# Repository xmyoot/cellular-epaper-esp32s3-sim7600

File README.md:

# Cellular ePaper — ESP32-S3 + SIM7600G-H

Revision B is an **engineering prototype under validation**. It is not released for fabrication or presented as a working, tested device. The portfolio case study remains unpublished pending validation.

This battery-powered design combines an ESP32-S3-WROOM-1-N8, SIM7600G-H LTE modem, GDEY029T94 2.9-inch monochrome ePaper panel interface, and SHT40 temperature/humidity sensor. It uses a protected 1S LiPo, switched modem/display supplies, native USB programming, and 1.8 V UART translation.

## Revision B changes

The initial review found an incorrect modem pinout and footprint, disconnected schematic pins, schematic/PCB disagreement, a SIM protection short, reversed LEDs, unsafe translator enable voltage, and an incompatible display power circuit. Revision B rebuilds the functional schematics and PCB from an explicit pin/net map. See [design report](DESIGN_REPORT.md) and [review results](review/README.md).

To simplify the power architecture, **the battery is charged externally**. USB-C is data/programming only; it does not power or charge the board. The original MCP73831 charger and its unresolved operation under system load have been removed. Use only a protected 1S pack capable of at least 3 A, verify connector polarity, and disconnect the pack for charging.

## Open in KiCad

Use KiCad 10 with the standard libraries installed. Open `Low-Power_Cellular_ePaper_Device_ESP32-S3_SIM7600.kicad_pro`. The project includes its custom 135-pad modem symbol/footprint and six functional schematic sheets. The board is 100 × 80 mm with four copper layers.

- [Component pin/net map](design/rev-b-netmap.json)
- [BOM](BOM.csv): engineering selections; procurement and assembly qualification remain open
- [Bring-up and validation procedure](design/VALIDATION.md)
- [Release status](review/release-status.json)

## CAD review artifacts

[Revision B schematic PDF](review/rev-b/schematic.pdf) · [PCB top CAD view](review/rev-b/pcb-top.png). Native checks report 0 ERC errors (1 retained library warning), 0 PCB DRC violations, 0 open connections and 0 schematic/PCB parity issues. Fabrication requires the [recorded via-in-pad process and stackup qualification](design/FABRICATION_CONSTRAINTS.md).

## Checks and release status

Run `python3 scripts/check_sources.py` for source consistency and `python3 scripts/check_hardware.py` for the audited critical connections. Regenerate native ERC/DRC reports using the commands in [review/README.md](review/README.md).

`python3 scripts/check_release.py` deliberately fails until all manufacturing and physical-validation gates are closed. A clean ERC/DRC result alone does not establish RF performance, battery life, display compatibility, or successful hardware operation.

Original manufacturing files, reports, and renders are retained only as explicitly marked historical material. Do not fabricate from those exports.

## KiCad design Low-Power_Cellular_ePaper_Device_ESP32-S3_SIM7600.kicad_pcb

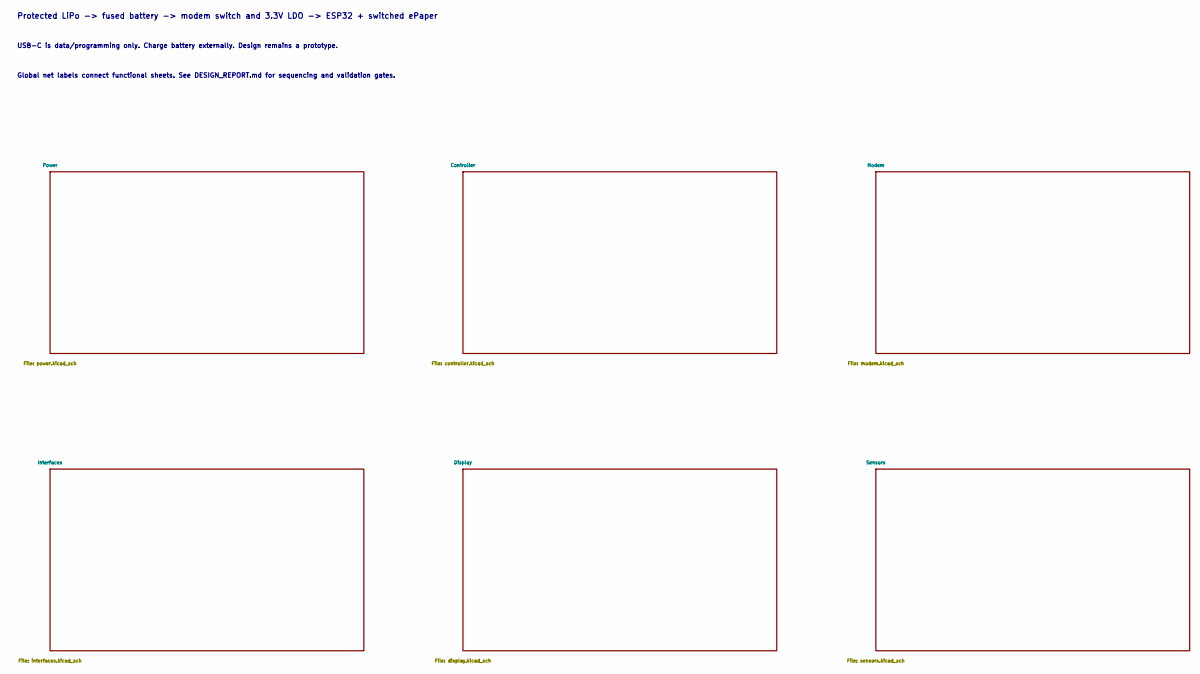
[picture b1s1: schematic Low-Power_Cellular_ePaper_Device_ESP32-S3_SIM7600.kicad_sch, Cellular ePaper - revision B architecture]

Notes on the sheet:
USB-C is data/programming only. Charge battery externally. Design remains a prototype.
Protected LiPo -> fused battery -> modem switch and 3.3V LDO -> ESP32 + switched ePaper
Global net labels connect functional sheets. See DESIGN_REPORT.md for sequencing and validation gates.

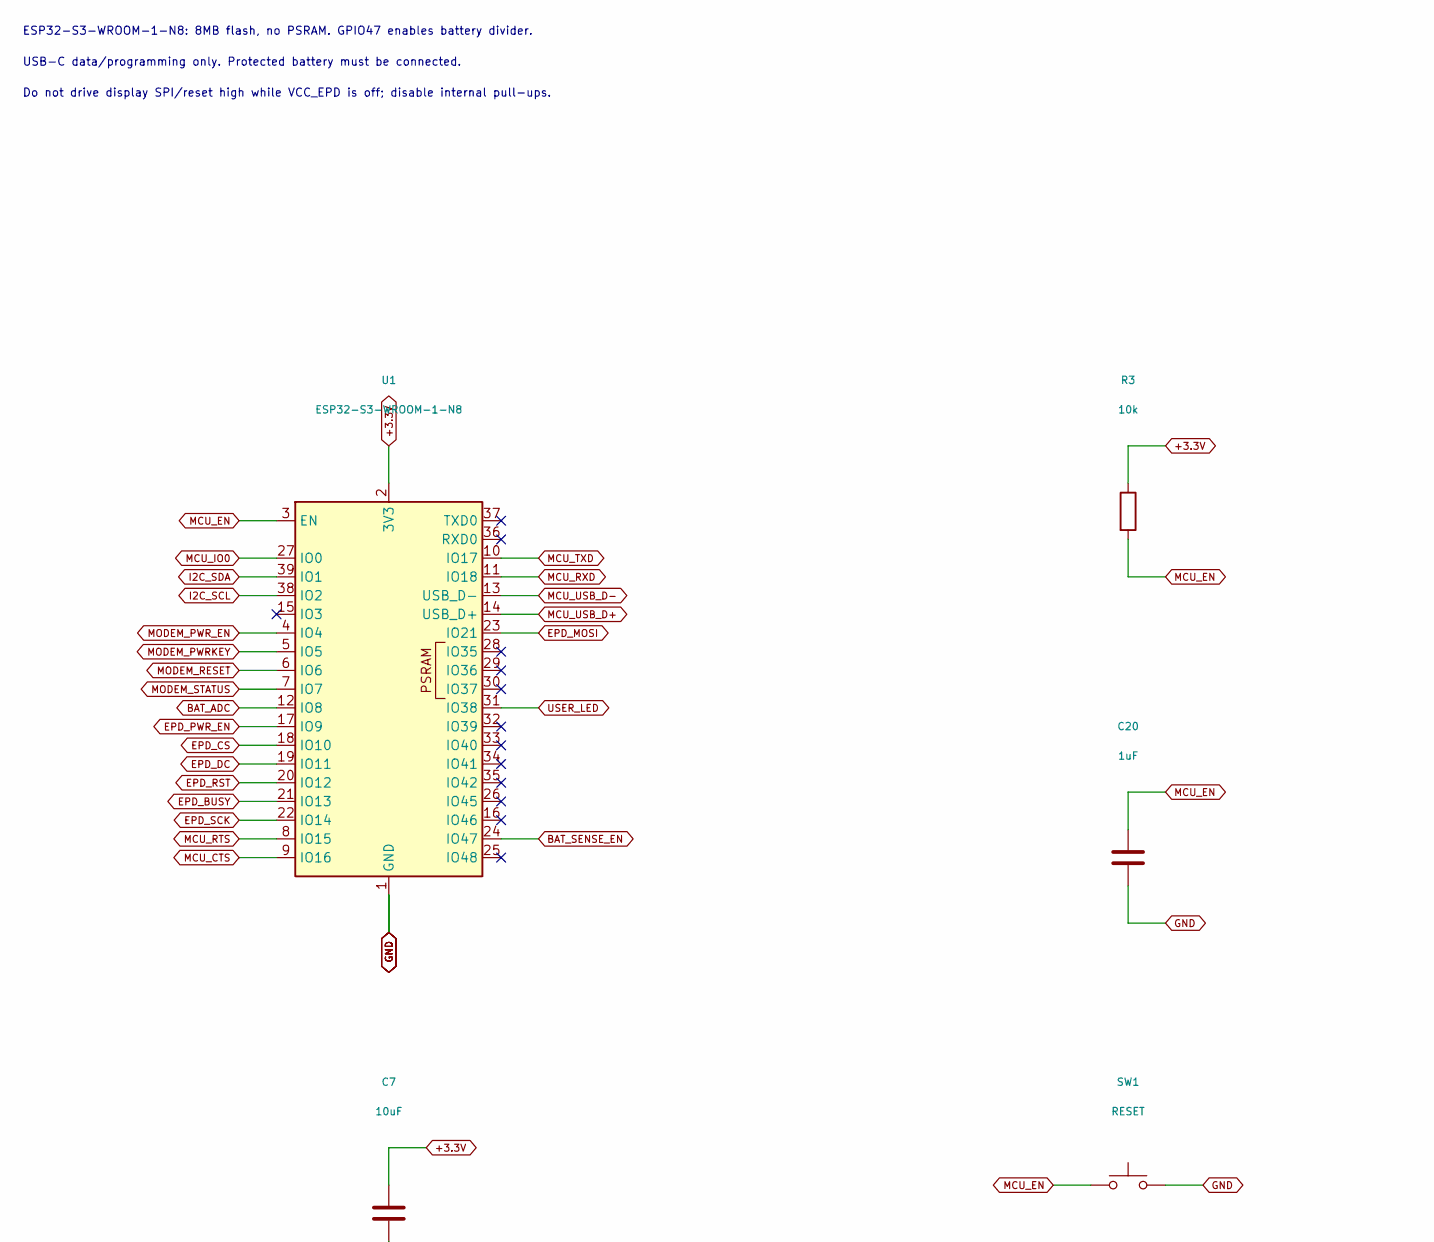
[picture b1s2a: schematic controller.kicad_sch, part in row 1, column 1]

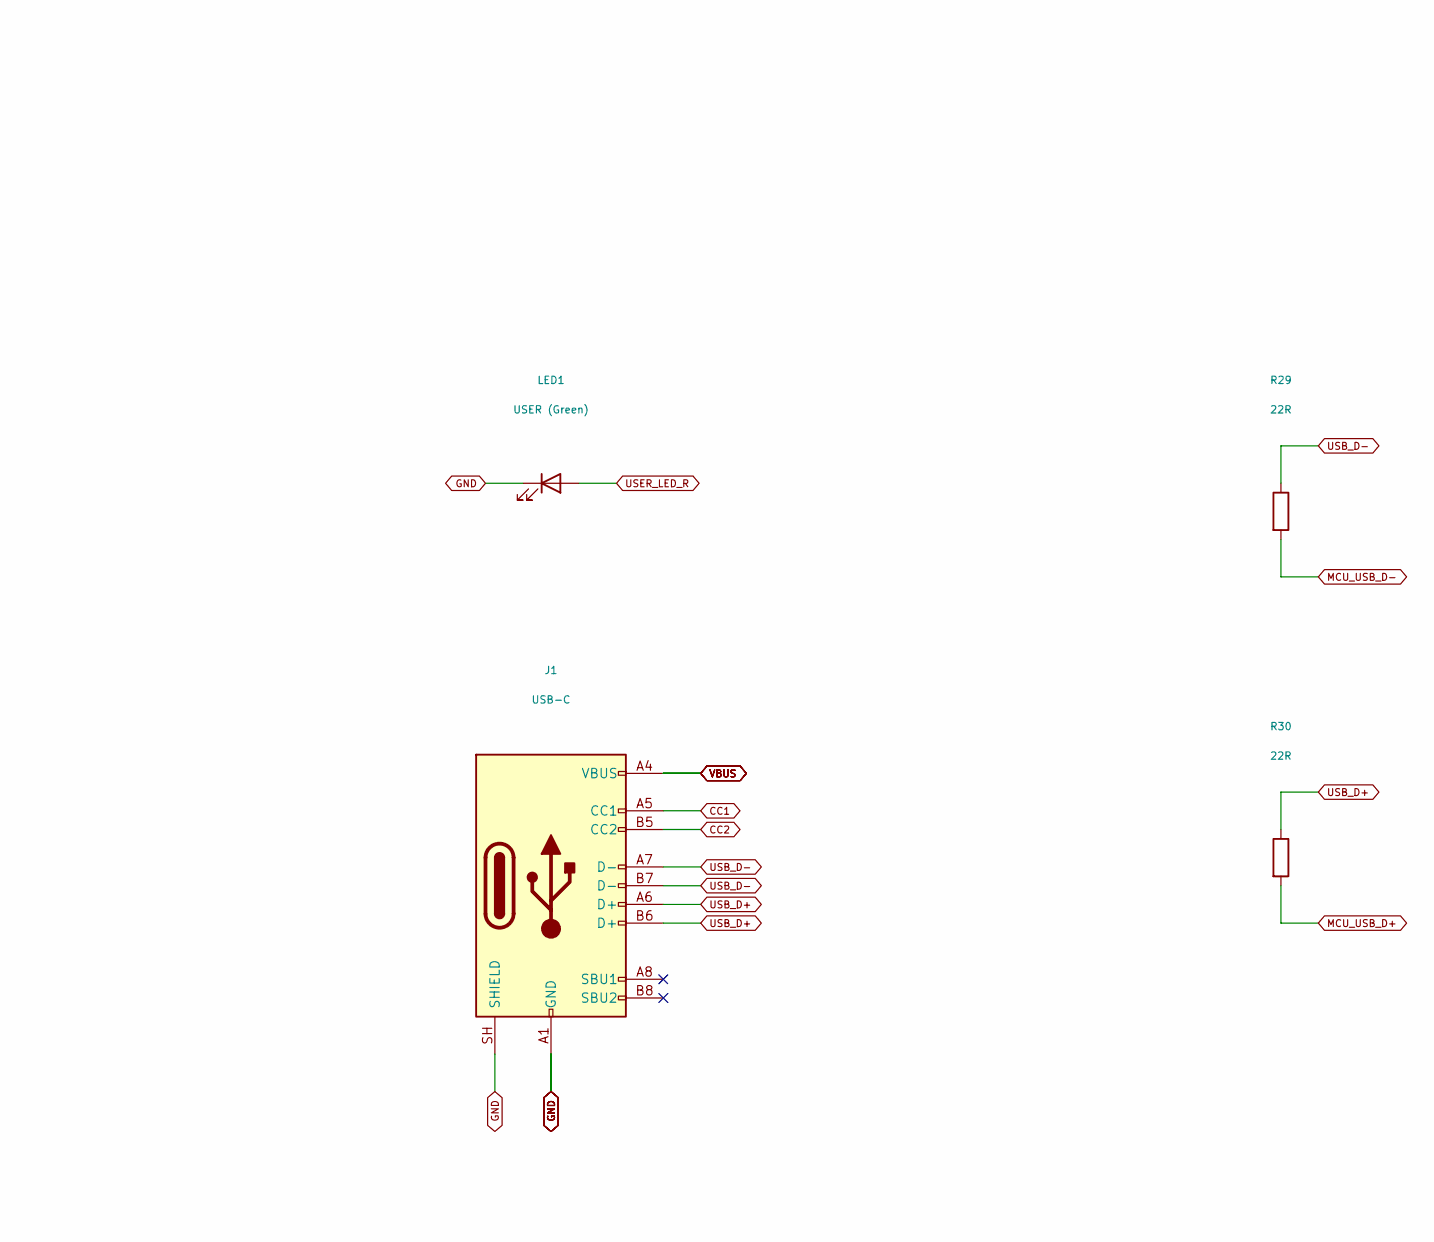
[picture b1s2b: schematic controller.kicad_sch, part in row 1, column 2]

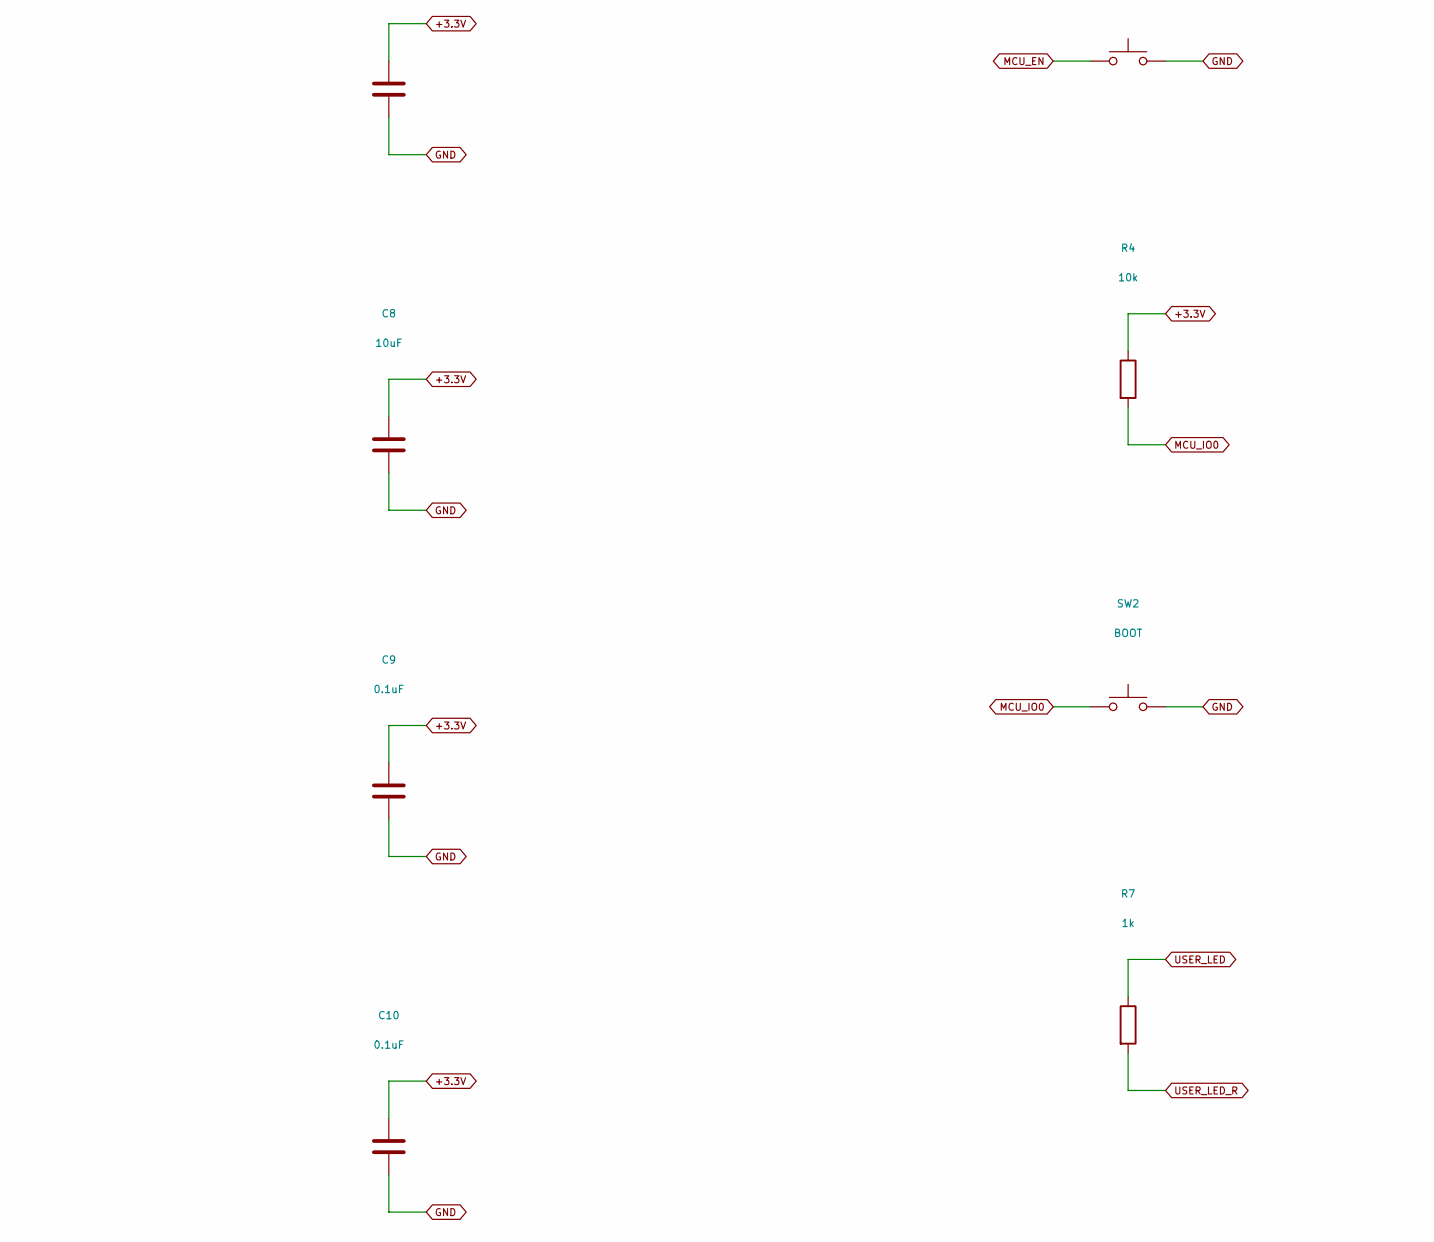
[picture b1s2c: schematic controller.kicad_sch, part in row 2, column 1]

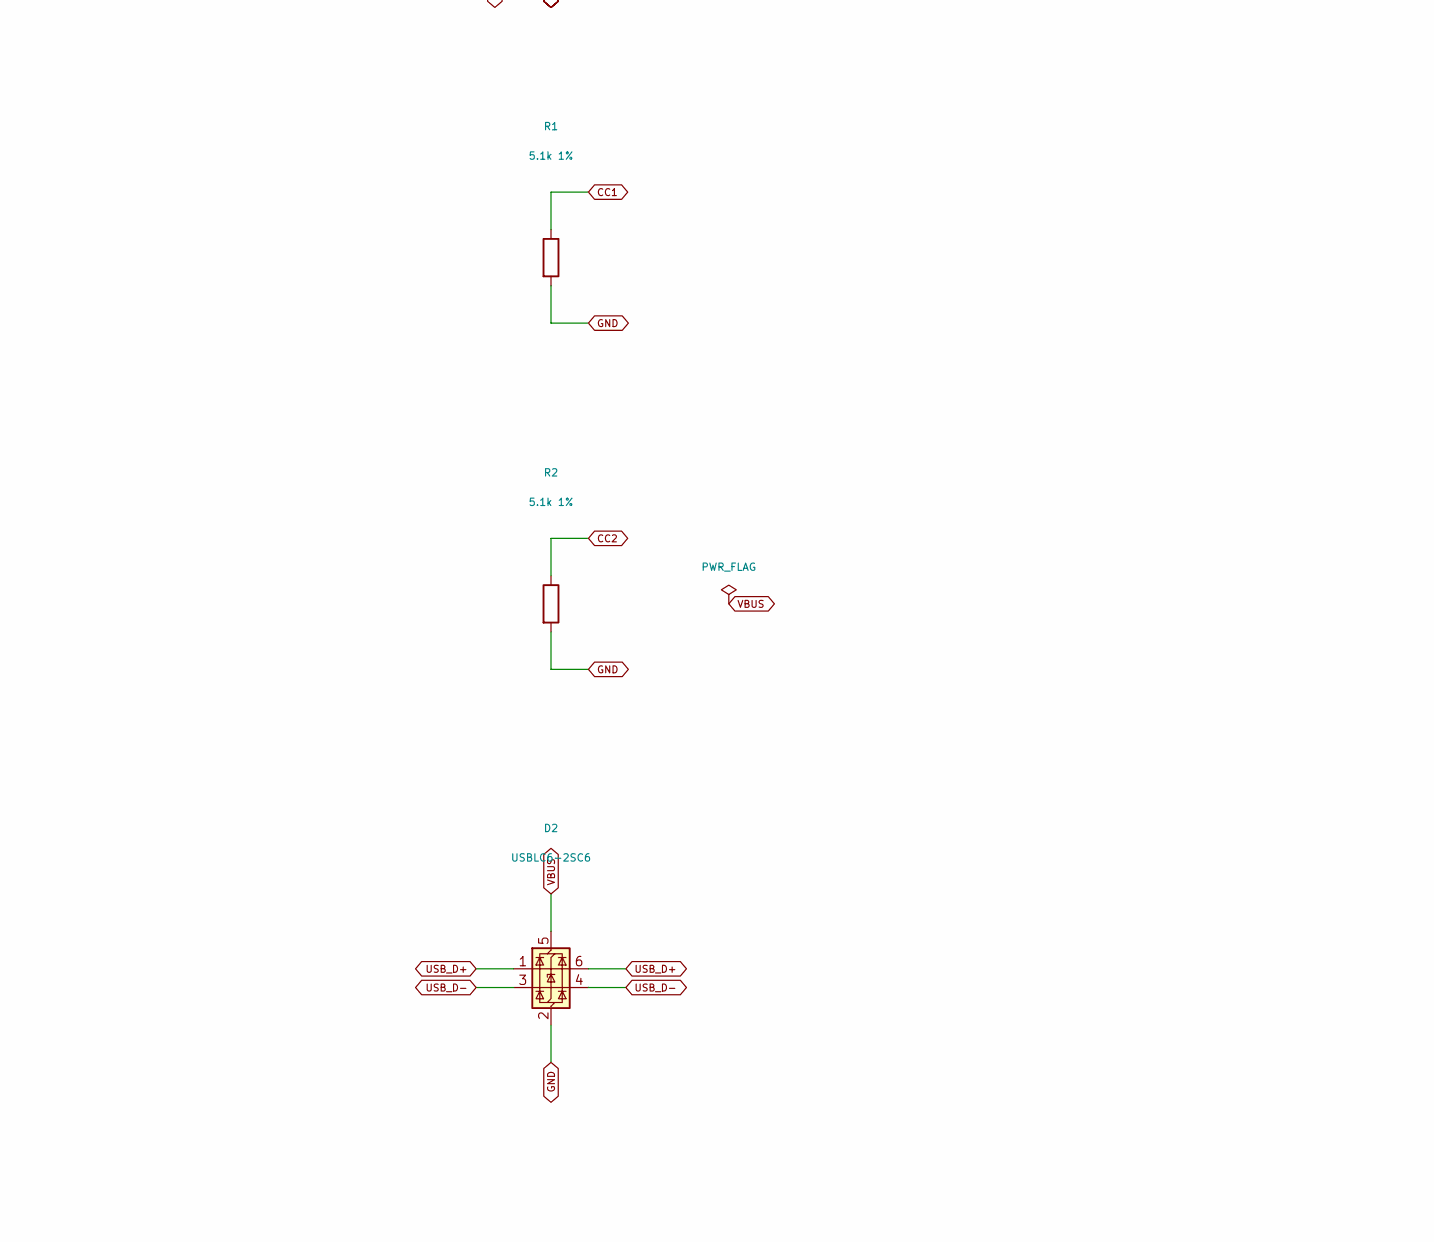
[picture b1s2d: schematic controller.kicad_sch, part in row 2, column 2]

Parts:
C7, C8: 10uF; C_0805_2012Metric
C9, C10: 0.1uF; C_0402_1005Metric
C20: 1uF; C_0603_1608Metric
D2: USBLC6-2SC6; SOT-23-6
J1: USB-C; USB4085_Edge
LED1: USER (Green); LED_0603_1608Metric
R1, R2: 5.1k 1%; R_0603_1608Metric
R3, R4: 10k; R_0603_1608Metric
R7: 1k; R_0603_1608Metric
R29, R30: 22R; R_0603_1608Metric
SW1: RESET; SW_Push_SPST_NO_Alps_SKRK
SW2: BOOT; SW_Push_SPST_NO_Alps_SKRK
U1: ESP32-S3-WROOM-1-N8; ESP32-S3-WROOM-1_Edge

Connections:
+3.3V: C7.1, C8.1, C9.1, C10.1, R3.1, R4.1, U1.2 (3V3); also elsewhere on the board
BAT_ADC: U1.12 (IO8); also elsewhere on the board
BAT_SENSE_EN: U1.24 (IO47); also elsewhere on the board
CC1: J1.A5 (CC1), R1.1
CC2: J1.B5 (CC2), R2.1
EPD_BUSY: U1.21 (IO13); also elsewhere on the board
EPD_CS: U1.18 (IO10); also elsewhere on the board
EPD_DC: U1.19 (IO11); also elsewhere on the board
EPD_MOSI: U1.23 (IO21); also elsewhere on the board
EPD_PWR_EN: U1.17 (IO9); also elsewhere on the board
EPD_RST: U1.20 (IO12); also elsewhere on the board
EPD_SCK: U1.22 (IO14); also elsewhere on the board
GND: C7.2, C8.2, C9.2, C10.2, C20.2, D2.2 (GND), J1.A1 (GND), J1.A12 (GND), J1.B1 (GND), J1.B12 (GND), J1.SH (SHIELD), LED1.1 (K), R1.2, R2.2, SW1.2, SW2.2, U1.1 (GND), U1.40 (GND), U1.41 (GND); also elsewhere on the board
I2C_SCL: U1.38 (IO2); also elsewhere on the board
I2C_SDA: U1.39 (IO1); also elsewhere on the board
MCU_CTS: U1.9 (IO16); also elsewhere on the board
MCU_EN: C20.1, R3.2, SW1.1, U1.3 (EN)
MCU_IO0: R4.2, SW2.1, U1.27 (IO0)
MCU_RTS: U1.8 (IO15); also elsewhere on the board
MCU_RXD: U1.11 (IO18); also elsewhere on the board
MCU_TXD: U1.10 (IO17); also elsewhere on the board
MCU_USB_D+: R30.2, U1.14 (USB_D+)
MCU_USB_D-: R29.2, U1.13 (USB_D-)
MODEM_PWRKEY: U1.5 (IO5); also elsewhere on the board
MODEM_PWR_EN: U1.4 (IO4); also elsewhere on the board
MODEM_RESET: U1.6 (IO6); also elsewhere on the board
MODEM_STATUS: U1.7 (IO7); also elsewhere on the board
USB_D+: D2.1 (I/O1), D2.6 (I/O1), J1.A6 (D+), J1.B6 (D+), R30.1
USB_D-: D2.3 (I/O2), D2.4 (I/O2), J1.A7 (D-), J1.B7 (D-), R29.1
USER_LED: R7.1, U1.31 (IO38)
USER_LED_R: LED1.2 (A), R7.2
VBUS: D2.5 (VBUS), J1.A4 (VBUS), J1.A9 (VBUS), J1.B4 (VBUS), J1.B9 (VBUS)

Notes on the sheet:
ESP32-S3-WROOM-1-N8: 8MB flash, no PSRAM. GPIO47 enables battery divider.
USB-C data/programming only. Protected battery must be connected.
Do not drive display SPI/reset high while VCC_EPD is off; disable internal pull-ups.

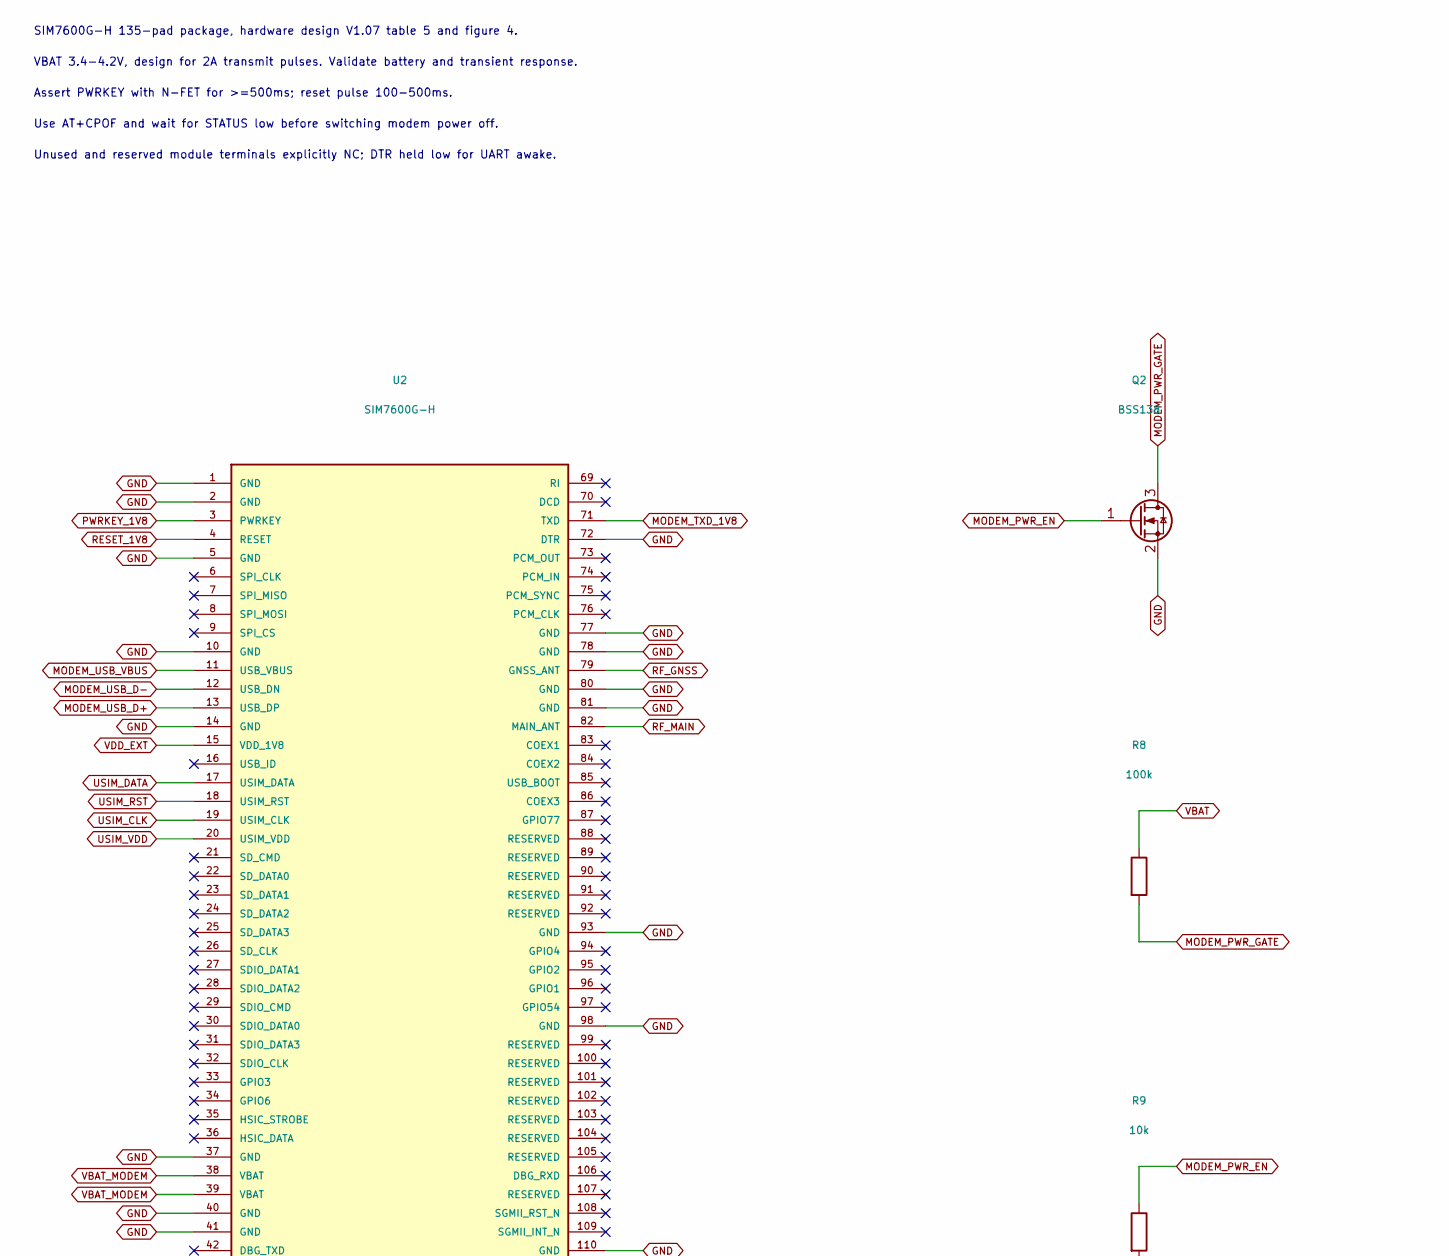
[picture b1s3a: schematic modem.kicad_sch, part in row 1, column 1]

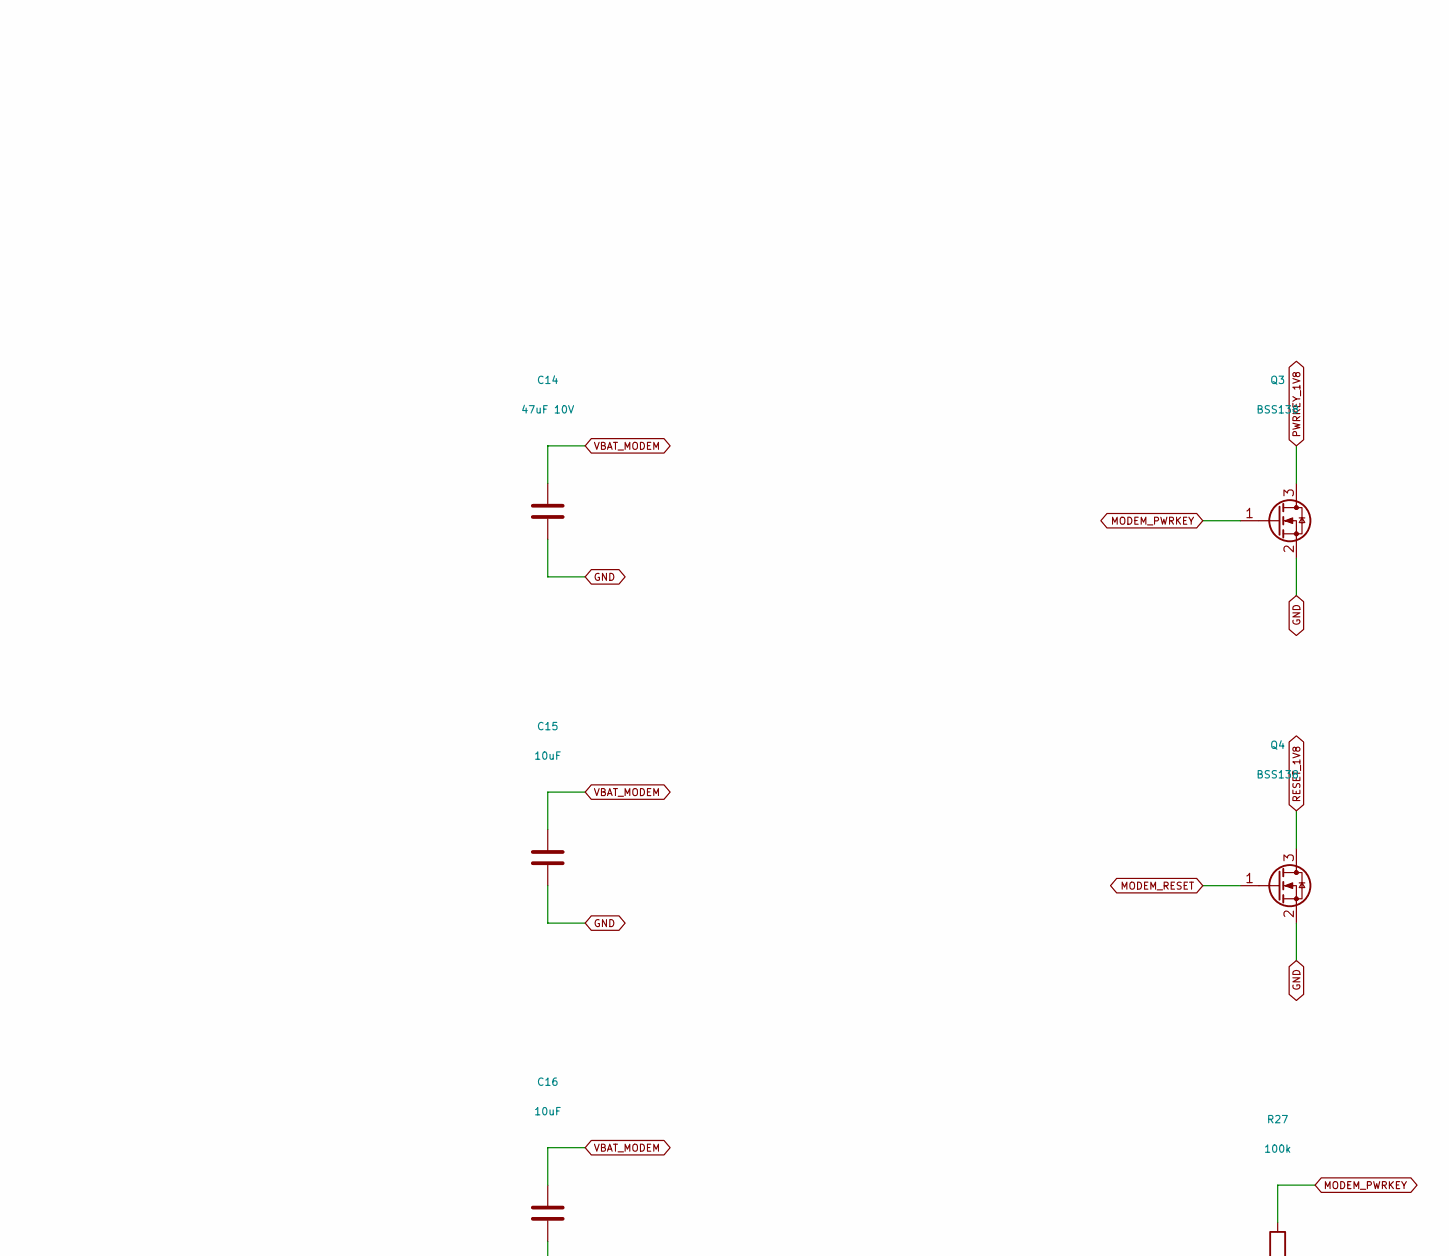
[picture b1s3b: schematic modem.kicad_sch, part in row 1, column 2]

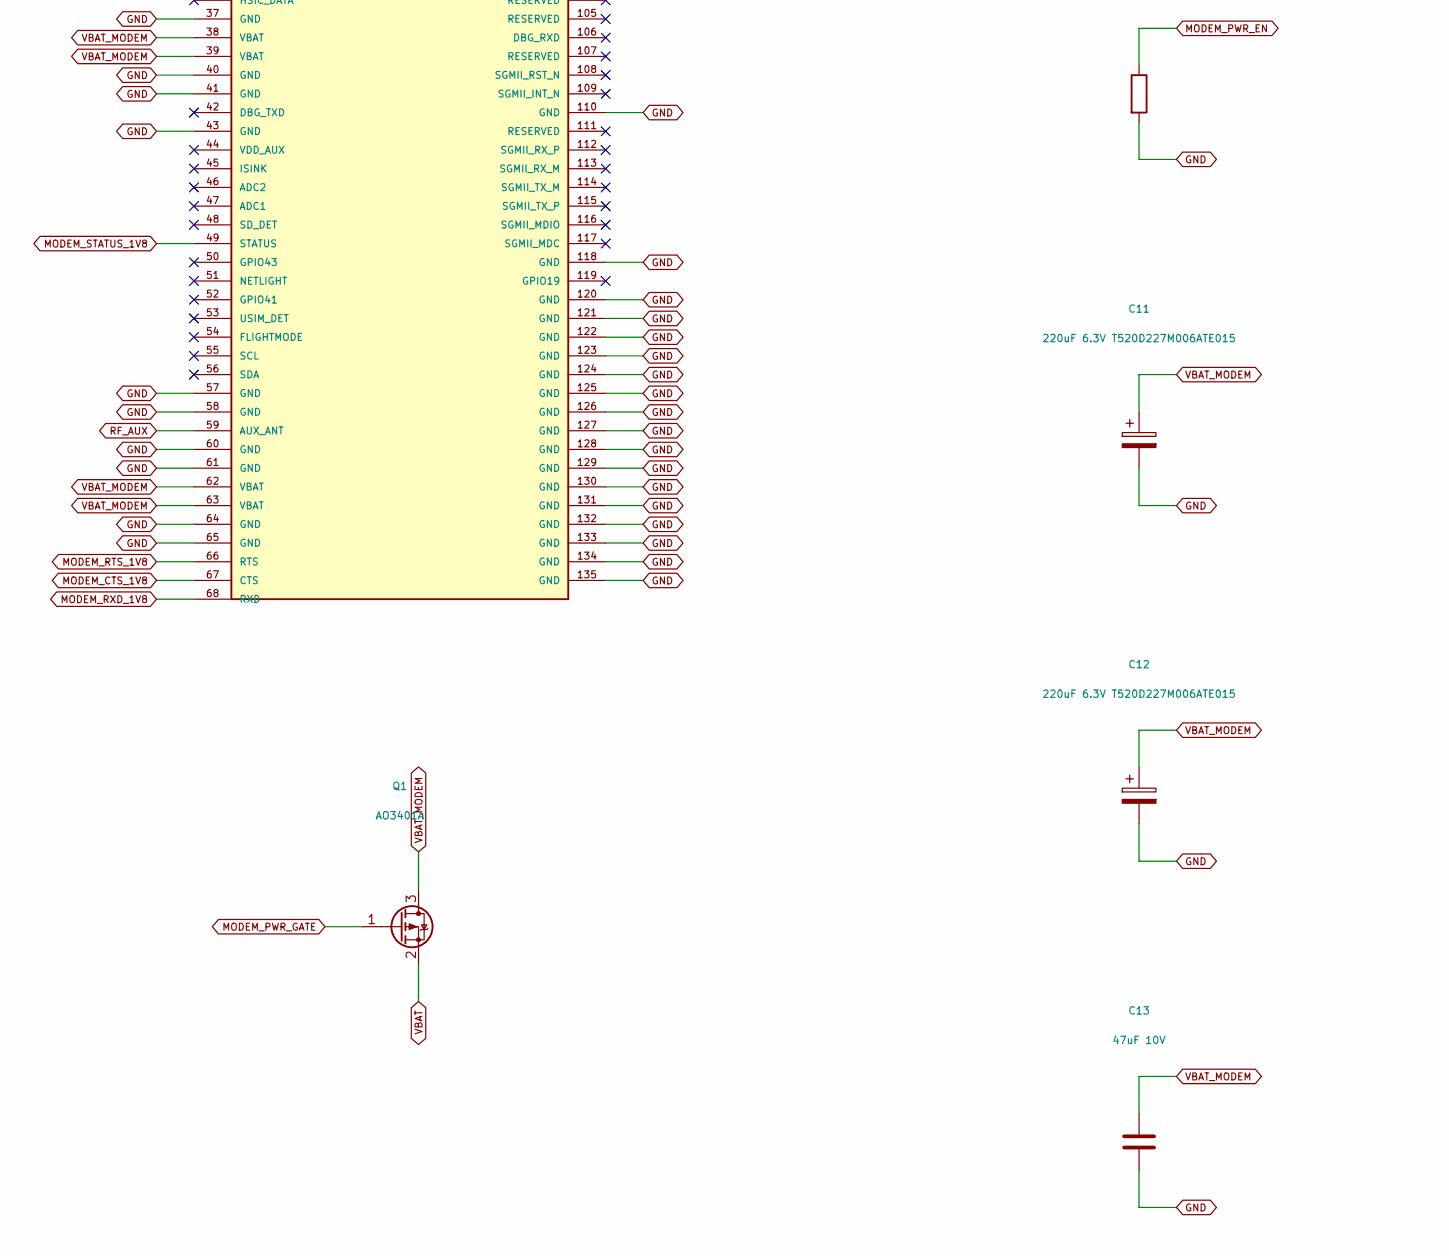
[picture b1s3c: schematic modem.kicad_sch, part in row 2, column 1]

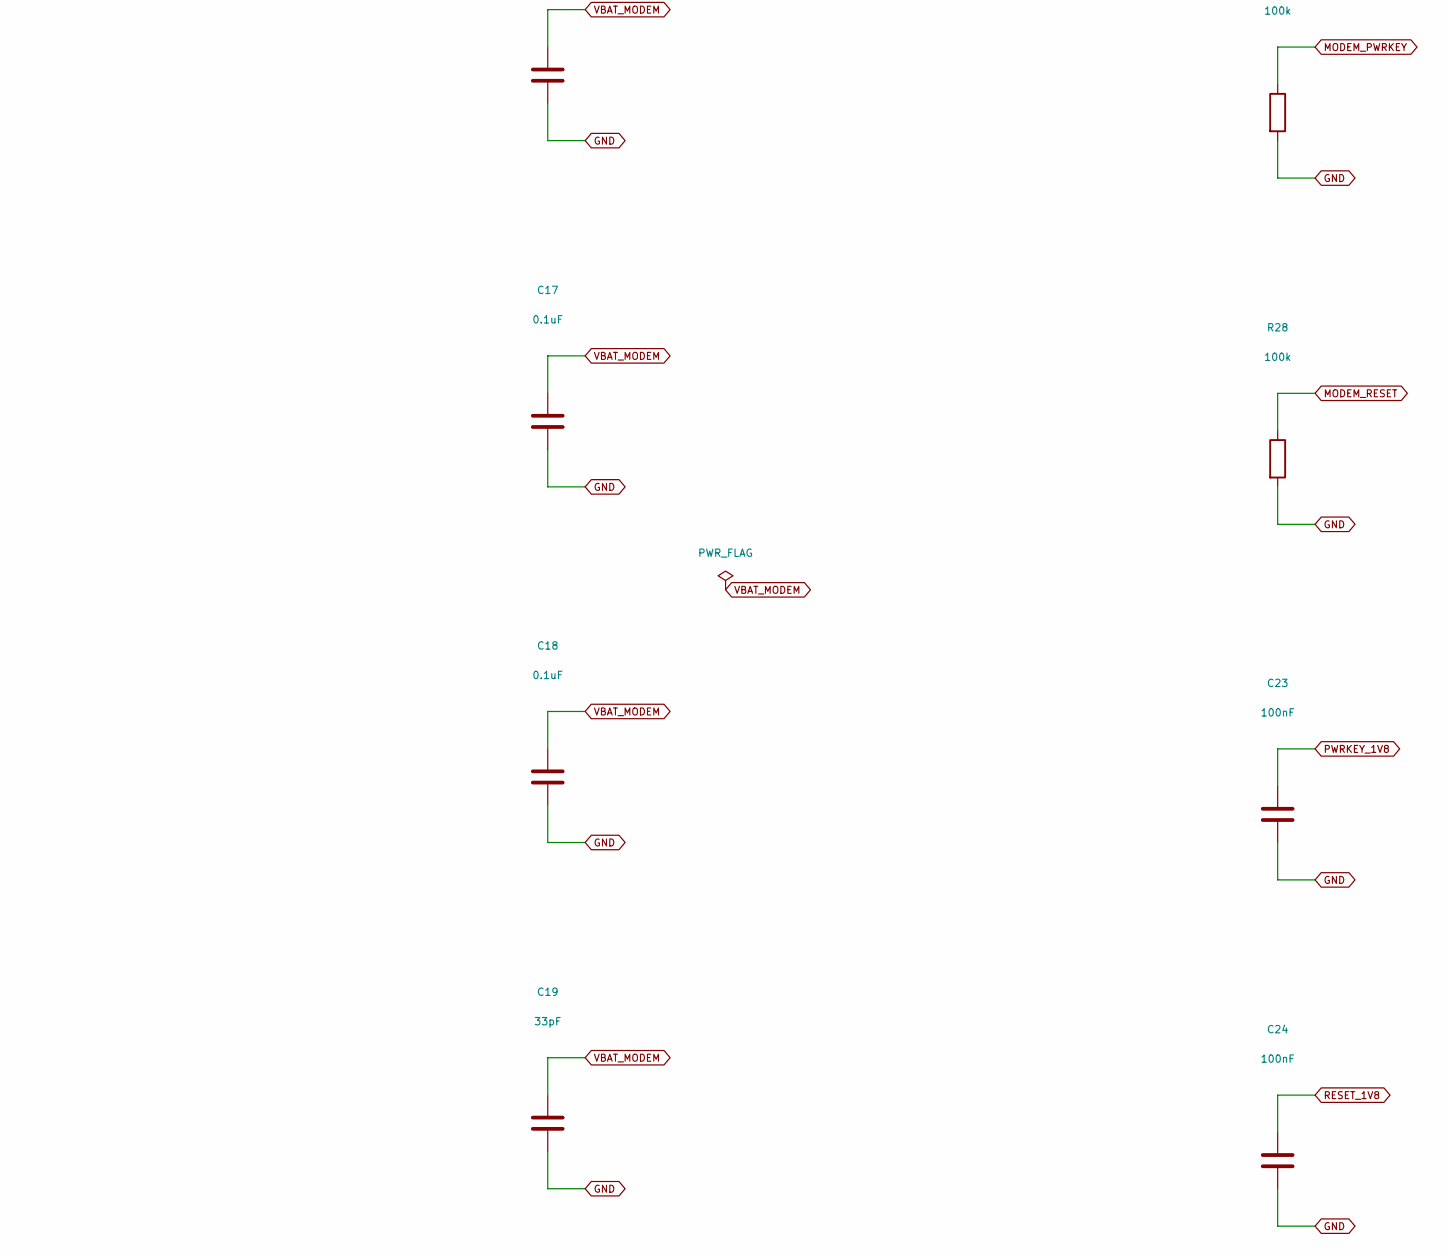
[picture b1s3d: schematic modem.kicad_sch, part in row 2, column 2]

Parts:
C11, C12: 220uF 6.3V T520D227M006ATE015; CP_EIA-7343-31_Kemet-D
C13, C14: 47uF 10V; C_0805_2012Metric
C15, C16: 10uF; C_0603_1608Metric
C17, C18: 0.1uF; C_0402_1005Metric
C19: 33pF; C_0402_1005Metric
C23, C24: 100nF; C_0402_1005Metric
Q1: AO3401A; SOT-23
Q2, Q3, Q4: BSS138; SOT-23
R8, R27, R28: 100k; R_0603_1608Metric
R9: 10k; R_0603_1608Metric
U2: SIM7600G-H; SIM7600G_H_135

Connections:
GND: C11.2, C12.2, C13.2, C14.2, C15.2, C16.2, C17.2, C18.2, C19.2, C23.2, C24.2, Q2.2 (S), Q3.2 (S), Q4.2 (S), R9.2, R27.2, R28.2, U2.1 (GND), U2.2 (GND), U2.5 (GND), U2.10 (GND), U2.14 (GND), U2.37 (GND), U2.40 (GND), U2.41 (GND), U2.43 (GND), U2.57 (GND), U2.58 (GND), U2.60 (GND), U2.61 (GND), U2.64 (GND), U2.65 (GND), U2.72 (DTR), U2.77 (GND), U2.78 (GND), U2.80 (GND), U2.81 (GND), U2.93 (GND), U2.98 (GND), U2.110 (GND), U2.118 (GND), U2.120 (GND), U2.121 (GND), U2.122 (GND), U2.123 (GND), U2.124 (GND), U2.125 (GND), U2.126 (GND), U2.127 (GND), U2.128 (GND), U2.129 (GND), U2.130 (GND), U2.131 (GND), U2.132 (GND), U2.133 (GND), U2.134 (GND), U2.135 (GND); also elsewhere on the board
MODEM_CTS_1V8: U2.67 (CTS); also elsewhere on the board
MODEM_PWRKEY: Q3.1 (G), R27.1; also elsewhere on the board
MODEM_PWR_EN: Q2.1 (G), R9.1; also elsewhere on the board
MODEM_PWR_GATE: Q1.1 (G), Q2.3 (D), R8.2
MODEM_RESET: Q4.1 (G), R28.1; also elsewhere on the board
MODEM_RTS_1V8: U2.66 (RTS); also elsewhere on the board
MODEM_RXD_1V8: U2.68 (RXD); also elsewhere on the board
MODEM_STATUS_1V8: U2.49 (STATUS); also elsewhere on the board
MODEM_TXD_1V8: U2.71 (TXD); also elsewhere on the board
MODEM_USB_D+: U2.13 (USB_DP); also elsewhere on the board
MODEM_USB_D-: U2.12 (USB_DN); also elsewhere on the board
MODEM_USB_VBUS: U2.11 (USB_VBUS); also elsewhere on the board
PWRKEY_1V8: C23.1, Q3.3 (D), U2.3 (PWRKEY)
RESET_1V8: C24.1, Q4.3 (D), U2.4 (RESET)
RF_AUX: U2.59 (AUX_ANT); also elsewhere on the board
RF_GNSS: U2.79 (GNSS_ANT); also elsewhere on the board
RF_MAIN: U2.82 (MAIN_ANT); also elsewhere on the board
USIM_CLK: U2.19 (USIM_CLK); also elsewhere on the board
USIM_DATA: U2.17 (USIM_DATA); also elsewhere on the board
USIM_RST: U2.18 (USIM_RST); also elsewhere on the board
USIM_VDD: U2.20 (USIM_VDD); also elsewhere on the board
VBAT: Q1.2 (S), R8.1; also elsewhere on the board
VBAT_MODEM: C11.1, C12.1, C13.1, C14.1, C15.1, C16.1, C17.1, C18.1, C19.1, Q1.3 (D), U2.38 (VBAT), U2.39 (VBAT), U2.62 (VBAT), U2.63 (VBAT)
VDD_EXT: U2.15 (VDD_1V8); also elsewhere on the board

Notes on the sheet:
Assert PWRKEY with N-FET for >=500ms; reset pulse 100-500ms.
Unused and reserved module terminals explicitly NC; DTR held low for UART awake.
Use AT+CPOF and wait for STATUS low before switching modem power off.
VBAT 3.4-4.2V, design for 2A transmit pulses. Validate battery and transient response.
SIM7600G-H 135-pad package, hardware design V1.07 table 5 and figure 4.
